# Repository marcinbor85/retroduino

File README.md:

# retroduino
Open hardware 8051-based arduino-compatible microcomputer

## Features
- Arduino-mega compatible pinout
- AT89S8253 based
- 32kB RAM for data memory
- 32kB RAM for program code
- 32kB EEPROM for non-volatile program code
- build-in bootloader (booting from ROM, copy EEPROM to RAM and run)
- USB PC connection (fast program code loading directly to RAM or to EEPROM)
- external data bus for external peripherals

## PCB

## Electric diagram

## Project purpose
- "because you can"

## Programming
- recommended SDCC compiler

## Memory layout

### Program bus
- 0x0000-0x2FFF - internal flash with bootloader
- 0x8000-0xFFFF - external program code memory
### Data bus
- 0x0000-0x00FF - internal ram
- 0x0100-0x7FFF - external peripherals
- 0x8000-0xFFFF - external data memory

## TODO
- [ ] external boards with digital and analog input/outputs
- [ ] PC application to loading code to the retroduino board
- [ ] bootloader with code loading, flashing, coping and app running
- [ ] example firmware applications

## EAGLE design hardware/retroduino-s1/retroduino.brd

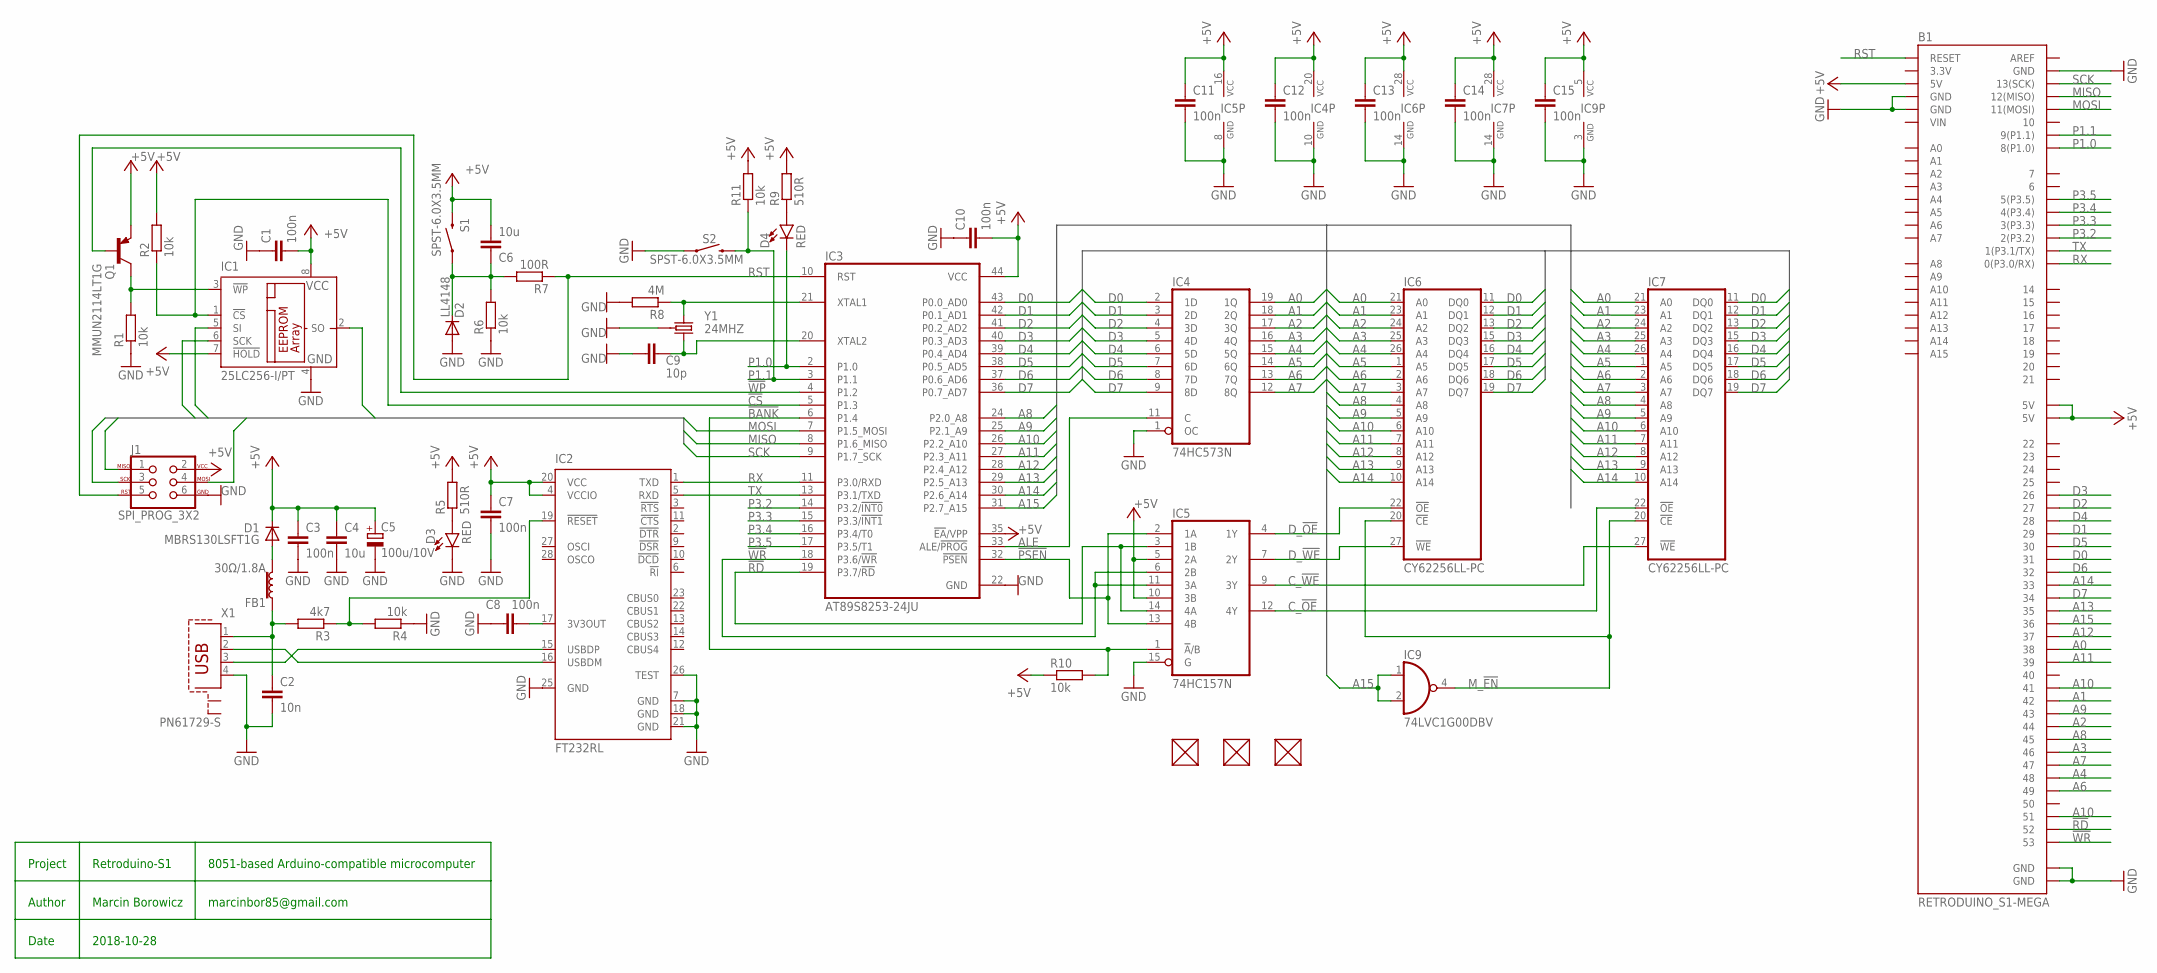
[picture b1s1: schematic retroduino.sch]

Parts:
B1: RETRODUINO_S1-MEGA; RETRODUINO_S1
C1, C3, C7, C8, C10, C11, C12, C13, C14, C15: 100n; C0603
C2: 10n; C0603
C4, C6: 10u; C1206
C5: 100u/10V; SMC_C
C9: 10p; C0603
D1: MBRS130LSFT1G; SOD123
D2: LL4148; MICROMELF-R
D3, D4: RED; LED-0603
FB1: 30Ω/1.8A; 0603
FUD1, FUD2, FUD3: FIDUCIAL; GHI_FIDUCIAL_40MIL
IC1: 25LC256-I/PT; DIL8
IC2: FT232RL; SSOP28
IC3: AT89S8253-24JU; S44
IC4: 74HC573N; DIL20
IC5: 74HC157N; DIL16
IC6, IC7: CY62256LL-PC; DIL28-6
IC9: 74LVC1G00DBV; SOT23-5
J1: SPI_PROG_3X2; 2X3-NS
Q1: MMUN2114LT1G; SOT23-BEC
R1, R2, R4, R6, R10, R11: 10k; R0603
R3: 4k7; R0603
R5, R9: 510R; R0603
R7: 100R; R0603
R8: 4M; R0603
S1, S2: SPST-6.0X3.5MM; TACTILE_SWITCH_SMD_6.0X3.5MM
X1: PN61729-S
Y1: 24MHZ; CRYSTAL-SMD-3.2X2.5MM

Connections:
!BANK: IC3.6 (P1.4), IC5.1 (!A!/B), R10.2
!CS: IC1.1 (!CS), IC3.5 (P1.3), R2.1
!PSEN: IC3.32 (!PSEN), IC5.2 (1A), IC5.13 (4B)
!RD: B1.52, IC3.19 (P3.7/!RD), IC5.3 (1B), IC5.14 (4A)
!WP: IC3.4 (P1.2), Q1.B
!WR: B1.53, IC3.18 (P3.6/!WR), IC5.6 (2B), IC5.11 (3A)
+5V: B1.5V@0 (5V), B1.5V@1 (5V), B1.5V@2 (5V), C1.2, C3.1, C4.1, C5.+, C6.1, C7.1, C10.2, C11.1, C12.1, C13.1, C14.1, C15.1, D1.C, IC1.7 (!HOLD), IC1.8 (VCC), IC2.4 (VCCIO), IC2.20 (VCC), IC3.35 (!EA!/VPP), IC3.44 (VCC), IC4.20 (VCC), IC5.5 (2A), IC5.10 (3B), IC5.16 (VCC), IC6.28 (VCC), IC7.28 (VCC), IC9.5 (VCC), J1.2, Q1.E, R2.2, R5.2, R9.2, R10.1, R11.2, S1.2
A0: B1.38, IC4.19 (1Q), IC6.21 (A0), IC7.21 (A0)
A1: B1.42, IC4.18 (2Q), IC6.23 (A1), IC7.23 (A1)
A2: B1.44, IC4.17 (3Q), IC6.24 (A2), IC7.24 (A2)
A3: B1.46, IC4.16 (4Q), IC6.25 (A3), IC7.25 (A3)
A4: B1.48, IC4.15 (5Q), IC6.26 (A4), IC7.26 (A4)
A5: IC4.14 (6Q), IC6.1 (A5), IC7.1 (A5)
A6: B1.49, IC4.13 (7Q), IC6.2 (A6), IC7.2 (A6)
A7: B1.47, IC4.12 (8Q), IC6.3 (A7), IC7.3 (A7)
A8: B1.45, IC3.24 (P2.0_A8), IC6.4 (A8), IC7.4 (A8)
A9: B1.43, IC3.25 (P2.1_A9), IC6.5 (A9), IC7.5 (A9)
A10: B1.41, B1.51, IC3.26 (P2.2_A10), IC6.6 (A10), IC7.6 (A10)
A11: B1.39, IC3.27 (P2.3_A11), IC6.7 (A11), IC7.7 (A11)
A12: B1.37, IC3.28 (P2.4_A12), IC6.8 (A12), IC7.8 (A12)
A13: B1.35, IC3.29 (P2.5_A13), IC6.9 (A13), IC7.9 (A13)
A14: B1.33, IC3.30 (P2.6_A14), IC6.10 (A14), IC7.10 (A14)
A15: B1.36, IC3.31 (P2.7_A15), IC9.1 (I0), IC9.2 (I1)
ALE: IC3.33 (ALE/!PROG), IC4.11 (C)
C_!OE: IC5.12 (4Y), IC7.22 (!OE)
C_!WE: IC5.9 (3Y), IC7.27 (!WE)
D0: B1.31, IC3.43 (P0.0_AD0), IC4.2 (1D), IC6.11 (DQ0), IC7.11 (DQ0)
D1: B1.29, IC3.42 (P0.1_AD1), IC4.3 (2D), IC6.12 (DQ1), IC7.12 (DQ1)
D2: B1.27, IC3.41 (P0.2_AD2), IC4.4 (3D), IC6.13 (DQ2), IC7.13 (DQ2)
D3: B1.26, IC3.40 (P0.3_AD3), IC4.5 (4D), IC6.15 (DQ3), IC7.15 (DQ3)
D4: B1.28, IC3.39 (P0.4_AD4), IC4.6 (5D), IC6.16 (DQ4), IC7.16 (DQ4)
D5: B1.30, IC3.38 (P0.5_AD5), IC4.7 (6D), IC6.17 (DQ5), IC7.17 (DQ5)
D6: B1.32, IC3.37 (P0.6_AD6), IC4.8 (7D), IC6.18 (DQ6), IC7.18 (DQ6)
D7: B1.34, IC3.36 (P0.7_AD7), IC4.9 (8D), IC6.19 (DQ7), IC7.19 (DQ7)
D_!OE: IC5.4 (1Y), IC6.22 (!OE)
D_!WE: IC5.7 (2Y), IC6.27 (!WE)
GND: B1.GND@0 (GND), B1.GND@1 (GND), B1.GND@2 (GND), B1.GND@3 (GND), B1.GND@4 (GND), C1.1, C2.2, C3.2, C4.2, C5.-, C7.2, C8.2, C9.1, C10.1, C11.2, C12.2, C13.2, C14.2, C15.2, D2.A, D3.C, IC1.4 (GND), IC2.7 (GND), IC2.18 (GND), IC2.21 (GND), IC2.25 (GND), IC2.26 (TEST), IC3.22 (GND), IC4.1 (OC), IC4.10 (GND), IC5.8 (GND), IC5.15 (G), IC6.14 (GND), IC7.14 (GND), IC9.3 (GND), J1.6, R1.1, R4.1, R6.1, R8.2, S2.1, X1.4, Y1.2 (3), Y1.4 (3)
MISO: B1.12 (12(MISO)), IC1.2 (SO), IC3.8 (P1.6_MISO), J1.1
MOSI: B1.11 (11(MOSI)), IC1.5 (SI), IC3.7 (P1.5_MOSI), J1.4
M_!EN: IC6.20 (!CE), IC7.20 (!CE), IC9.4 (O)
unnamed: C9.2, IC3.20 (XTAL2), Y1.3 (2)
unnamed: IC3.21 (XTAL1), R8.1, Y1.1
unnamed: C6.2, D2.C, R6.2, R7.2, S1.1
unnamed: D3.A, R5.1
unnamed: D4.A, R9.1
unnamed: IC2.16 (USBDM), X1.2
unnamed: C8.1, IC2.17 (3V3OUT)
unnamed: IC2.15 (USBDP), X1.3
unnamed: C2.1, FB1.1, R3.2, X1.1
unnamed: IC1.3 (!WP), Q1.C, R1.2
unnamed: D1.A, FB1.2
unnamed: IC2.19 (!RESET), R3.1, R4.2
P1.0: B1.8 (8(P1.0)), D4.C, IC3.2 (P1.0)
P1.1: B1.9 (9(P1.1)), IC3.3 (P1.1), R11.1, S2.2
P3.2: B1.2 (2(P3.2)), IC3.14 (P3.2/!INT0)
P3.3: B1.3 (3(P3.3)), IC3.15 (P3.3/!INT1)
P3.4: B1.4 (4(P3.4)), IC3.16 (P3.4/T0)
P3.5: B1.5 (5(P3.5)), IC3.17 (P3.5/T1)
RST: B1.RESET, IC3.10 (RST), J1.5, R7.1
RX: B1.0 (0(P3.0/RX)), IC2.1 (TXD), IC3.11 (P3.0/RXD)
SCK: B1.13 (13(SCK)), IC1.6 (SCK), IC3.9 (P1.7_SCK), J1.3
TX: B1.1 (1(P3.1/TX)), IC2.5 (RXD), IC3.13 (P3.1/TXD)

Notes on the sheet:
Author
Project
Date
Marcin Borowicz
Retroduino-S1
2018-10-28
8051-based Arduino-compatible microcomputer
marcinbor85@gmail.com

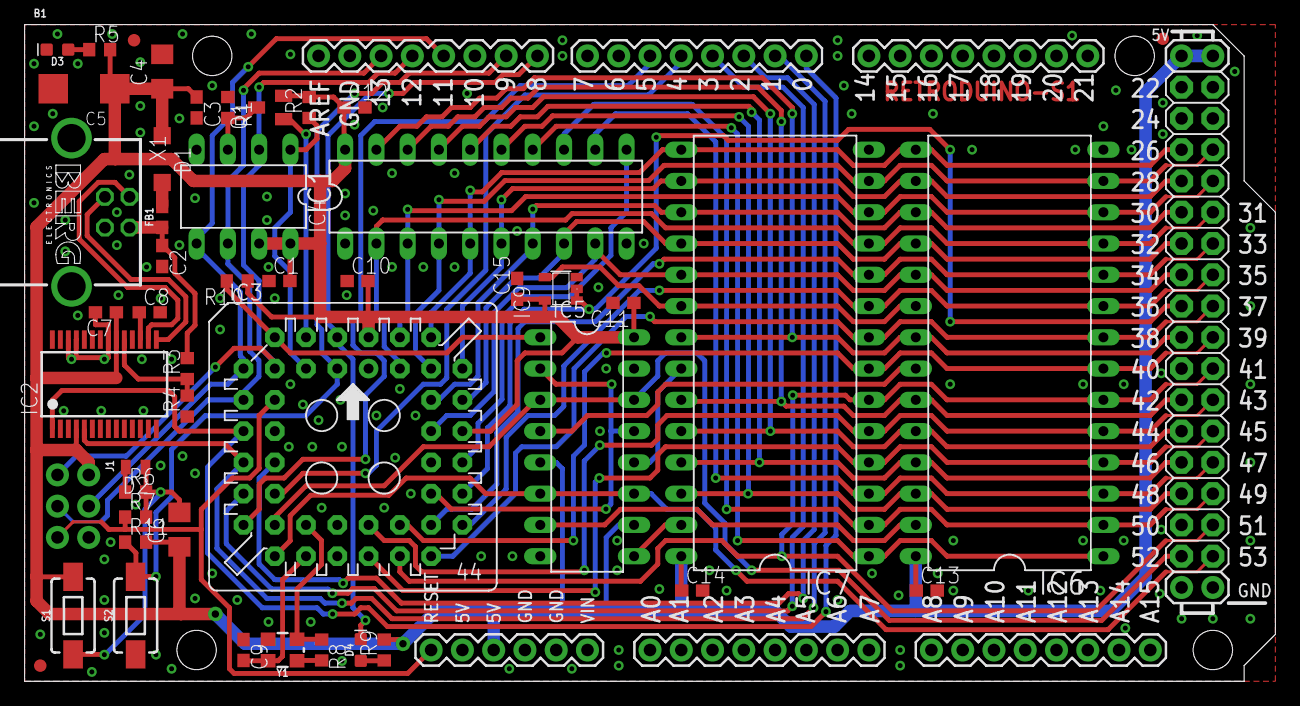
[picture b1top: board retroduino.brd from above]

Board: 2 copper layers, 101.6 x 53.3 mm, 49 parts (0 on the bottom side), 62 nets.

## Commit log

2018-10-28 change license type
2018-10-28 pcb project added
2018-10-28 readme file updated
2018-10-28 diagram and assets updated
2018-10-28 readme updated
2018-11-01 dodany email na schemacie
2018-11-01 dodany szablon bootloadera wraz z makefilem pod sdcc
2018-11-04 dodane ustawienia vs
2018-11-04 rozbudowany szablon aplikacji
2018-11-04 usuniete ustawienia środowiska (takie same jak domyślne)
2018-11-04 założony workspace ze wsyztskimi projektami do retroduino
2018-11-04 dodany przykład z prostym led blinkiem
2018-11-04 dodany przykład z zaawansowanym led blinkiem
2018-11-04 poprawki
2018-11-09 dodane gerbery
2019-02-08 test memory example project template added `
2019-02-09 improvements
2019-02-09 unsigned int bug fix
2019-02-09 some pcb bugs fixed:
    1. !ea should be connected to vcc due to allow boot from internal flash
    2. missing microcontroller gnd supply (pin 22)

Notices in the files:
parts and their libraries:
SparkFun-Connectors: Licensing: Creative Commons ShareAlike 4.0 International - https://creativecommons.org/licenses/by-sa/4.0
